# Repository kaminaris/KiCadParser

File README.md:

# kicad-io

TypeScript library for parsing, modifying, and serialising KiCad S-expression
files (`.kicad_sch`, `.kicad_pcb`, `.kicad_sym`).

The library is **source-only** — there is no root `package.json`. Consuming
projects reference it via TypeScript project references (`tsconfig.json`
`references` array).

---

## Overview

KiCad stores schematics, boards, and symbol libraries as S-expression (sexpr)
text files.  This library turns those files into a typed, navigable tree of
`KicadElement` objects, lets you inspect and modify the tree, and writes it
back to a valid KiCad file.

```
parse(text) → KicadElement tree → mutate → element.write() → text
```

---

## Structure

```
src/
  KicadParser.ts          # tokeniser + recursive-descent S-expr parser
  KicadElement.ts         # base class for every tree node
  KicadElement*.ts        # ~70 typed element subclasses
  Project/
    KicadSExprFile.ts     # abstract base: load → parse → write
    KicadSchematic.ts     # .kicad_sch loader, resolves hierarchical sheets
    KicadBoard.ts         # .kicad_pcb loader
    KicadProject.ts       # ties a schematic + board together
    SymbolBOMInterface.ts # BOM row shape + groupBOM() helper
    PathUtils.ts          # platform-agnostic path helpers
  Builder/
    PassiveSymbolBuilder.ts   # entry point – re-exports all builder APIs
    PassiveSymbolFromSpec.ts  # build a Device:* symbol from a spec object
    PassiveSymbolManualVariants.ts
    PassiveSymbolPrimitives.ts
    PassiveSymbolRegistry.ts
    PassiveSymbolTypes.ts
  Catalog/
    DeviceSymbolSpecs.ts      # geometry specs extracted from real KiCad files
    DevicePassiveSymbols.ts
    DeviceSymbolSpecTypes.ts
examples/                 # six runnable, heavily-commented example scripts
test/                     # vitest test suite
```

---

## Core API

### `KicadParser`

```ts
import { KicadParser } from './src/KicadParser';

const parser = new KicadParser();
const root = parser.parse(fileText);  // returns KicadElement
```

The parser recognises ~80 named element types via its `nodeMap` and
instantiates the appropriate subclass for each.  Unknown element names fall
back to the base `KicadElement`.

A `contextualNodeMap` handles the handful of element names whose meaning
depends on their parent (e.g. `unit` inside `units` vs. `unit` on a symbol
instance).

### `KicadElement`

The base class for every node in the tree.

| Method | Description |
|---|---|
| `findFirstChildByClass(Cls)` | First direct child that is an instance of `Cls` |
| `findChildrenByClass(Cls)` | All direct children that are instances of `Cls` |
| `findAllChildrenByClass(Cls)` | Deep search for all descendants of type `Cls` |
| `findOrCreateChildByClass(Cls)` | Find or lazily create a child of type `Cls` |
| `findFirstChildByName(name)` | First direct child with the given element name |
| `findAllChildrenByName(name)` | Deep search by element name |
| `setSimpleChild(name, value, format)` | Set/create a single-attribute leaf child |
| `getSimpleChildValue(name)` | Read the first attribute of a named child |
| `addChild(node)` | Append a child (sets `parent` + `rootLevel`) |
| `write()` | Serialise this node and all descendants back to KiCad text |

### Loading a file (`KicadSExprFile`)

The loader is I/O-agnostic — you supply a `loadFile` callback so the same code
works in Node.js, a browser, or any other runtime.

```ts
import { KicadSchematic } from './src/Project/KicadSchematic';

const sch = new KicadSchematic();
sch.loadFile = (path) => fs.promises.readFile(path, 'utf8');
sch.pathUtils = { dirname: (p) => path.dirname(p), join: (...parts) => path.join(...parts) };
await sch.loadFromPath('/path/to/my.kicad_sch');

const root = sch.rootElement!;
// navigate / modify ...
const updated = root.write();
await fs.promises.writeFile('/path/to/my.kicad_sch', updated, 'utf8');
```

### Loading a hierarchical project (`KicadProject`)

```ts
import { KicadProject } from './src/Project/KicadProject';

const project = new KicadProject();
await project.loadFromPath(loadFile, pathUtils, 'root.kicad_sch', 'board.kicad_pcb');

const schematic = project.mainSchematic!;
const board     = project.mainBoard!;
```

`KicadSchematic` automatically follows `sheet` references and populates
`schematic.sheets` with the parsed child schematics.

### Programmatic symbol building (`Builder`)

```ts
import { buildDeviceSymbolFromSpec } from './src/Builder/PassiveSymbolBuilder';

const symbol = buildDeviceSymbolFromSpec('R', '100k', '0402');
libSymbols.addChild(symbol);
```

See `examples/06-add-footprint-with-3d-model.ts` for a full walkthrough.

---

## Examples

Self-contained, runnable scripts in `examples/`:

```sh
cd examples
yarn install
yarn 01   # parse a schematic, list placed symbols
yarn 02   # parse a board, list layers + footprints
yarn 03   # load, modify a symbol's Value, write back out
yarn 04   # build a board layer stackup from scratch
yarn 05   # load a hierarchical multi-sheet project, print a BOM
yarn 06   # add a footprint with a 3D model reference from scratch
```

---

## Tests

```sh
cd test
yarn install
yarn test          # run once
yarn test:watch    # watch mode
```

The test suite uses [Vitest](https://vitest.dev/) and covers the tokeniser,
parser round-trips, element builders, and real-world KiCad 10 fixture files.

---

## License

MIT — see [LICENSE](LICENSE).

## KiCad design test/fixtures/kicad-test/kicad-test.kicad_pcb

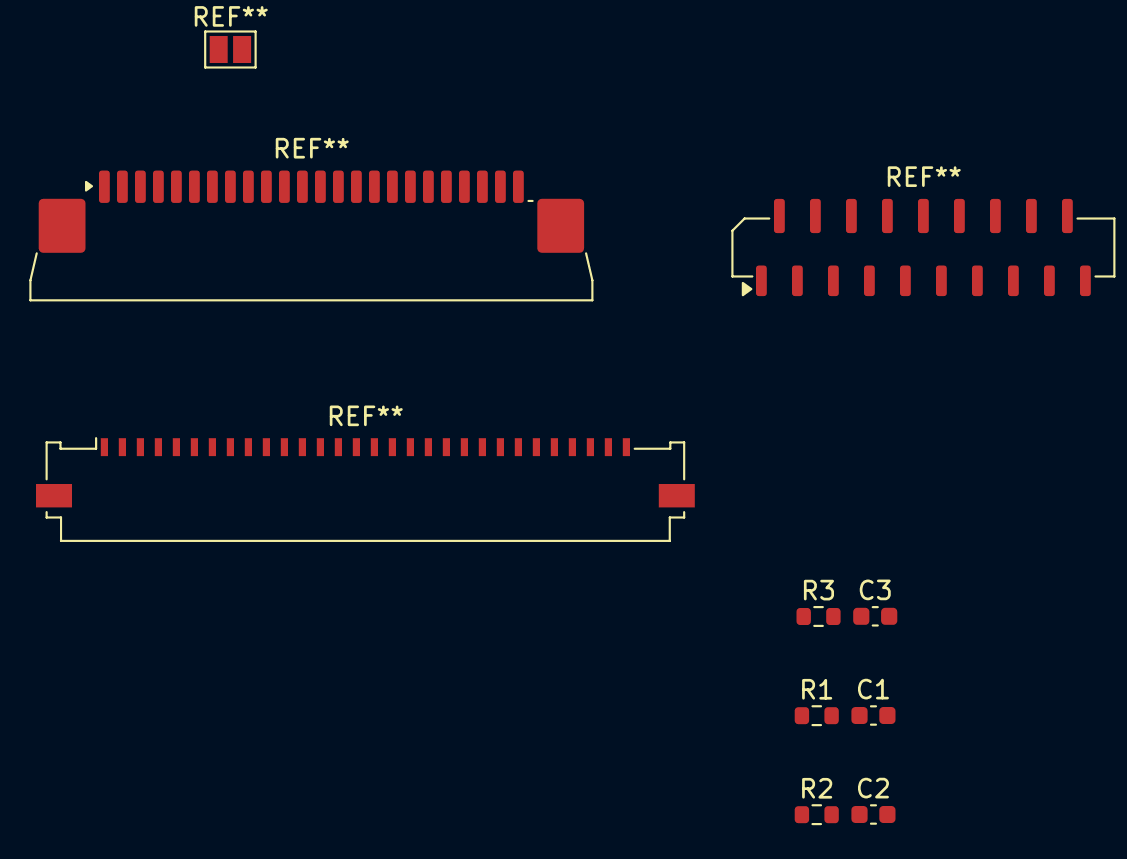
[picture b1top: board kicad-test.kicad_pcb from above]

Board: 2 copper layers, 6 parts (0 on the bottom side), 5 nets, no tracks yet.

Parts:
C1, C2, C3: C; C_0603_1608Metric
R1, R2, R3: R; R_0603_1608Metric

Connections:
+3.3V: R1.1, R2.1, R3.1
/TestSheet1/hiera: C1.1, R1.2
/TestSheet2/hiera: C2.1, R2.2
/TestSheet3/hiera: C3.1, R3.2
GND: C1.2, C2.2, C3.2

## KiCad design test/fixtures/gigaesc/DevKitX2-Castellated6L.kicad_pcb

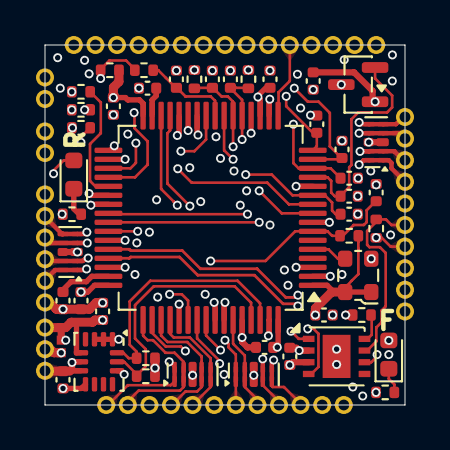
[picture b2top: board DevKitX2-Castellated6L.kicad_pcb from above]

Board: 6 copper layers, 20.0 x 20.0 mm, 47 parts (0 on the bottom side), 65 nets.

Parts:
C1, C2, C3, C25, C26, C27, C28, C47, C48, C49: 100n; C_0402_1005Metric
C5, C6, C15, C16, C17, C18, C19, C20: 1u; C_0402_1005Metric
C29, C30: 1n; C_0402_1005Metric
D1: L RUN; LED_0603_1608Metric
D2: L FAULT; LED_0603_1608Metric
J4: X3.0CH-Master
JP3: VSel; SolderJumper-3-0.5-Small
R1, R2: 3.3k; R_0402_1005Metric
R3, R10, R11, R12, R13, R14: 10k; R_0402_1005Metric
R4: 120; R_0402_1005Metric
R8, R9: 100k; R_0402_1005Metric
R15, R16, R17: 1k; R_0402_1005Metric
U1: LSM6DS3TR-C; LGA-14_3x2.5mm_P0.5mm
U2: SIT3051; DFN-8-1EP_3x3mm_P0.65mm_EP1.55x2.4mm
U3: REF3033AIDBZR; SOT-23
U4, U5, U7, U8: PESD4USB5U-TTSX; Diodes_UDFN-10_1x2.5mm_P0.5mm
U6: STM32F405RGT6; LQFP-64_10x10mm_P0.5mm
Y1: SX2M8.000M20F30TNN; Oscillator_SMD_ECS_2520MV-xxx-xx-4Pin_2.5x2.0mm

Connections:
+3.3REF: C6.1, U3.2 (Vout), U6.13 (VDDA)
+3.3V: C1.1, C2.1, C3.1, C17.1, C18.1, C19.1, C20.1, C47.1, J4.11 (3.3V), JP3.1 (A), R1.1, R2.1, R10.1, R13.2, U1.5 (VDDIO), U1.8 (VDD), U1.12 (CS), U2.3 (VDD), U6.1 (VBAT), U6.19 (VDD), U6.32 (VDD), U6.48 (VDD), U6.64 (VDD), Y1.1 (Tri-State), Y1.4 (VDD)
+5V: C5.1, J4.12 (5V), JP3.3 (B), U3.1 (Vin)
CAN RX: U2.4 (RXD), U6.57 (PB5)
CAN TX: U2.1 (TXD), U6.58 (PB6)
CURR1 FILTERED: J4.37 (CURRENT1), U6.8 (PC0)
CURR2 FILTERED: J4.42 (CURRENT2), U6.9 (PC1)
CURR3 FILTERED: J4.47 (CURRENT3), U6.10 (PC2)
ESP-RX: J4.18 (U1-RX), U6.52 (PC11), U7.5, U7.6
ESP-TX: J4.17 (U1-TX), U6.51 (PC10), U7.4, U7.7
GND: C1.2, C2.2, C3.2, C5.2, C6.2, C15.2, C16.2, C17.2, C18.2, C19.2, C20.2, C25.2, C29.2, C30.2, C47.2, C48.2, C49.2, J4.3 (GND), J4.10 (GND), J4.13 (GND), J4.16 (GND), J4.28 (GND), J4.31 (GND), R3.1, R8.1, R9.2, R11.2, R12.2, U1.1 (SDO/SA0), U1.2 (SDX), U1.3 (SCX), U1.6 (GND), U1.7 (GND), U2.2 (VSS), U2.9 (VSS), U3.3 (GND), U4.3 (VSS), U4.8 (VSS), U5.3 (VSS), U5.8 (VSS), U6.12 (VSSA), U6.18 (VSS), U6.28 (PB2), U6.60 (BOOT0), U6.63 (VSS), U7.3 (VSS), U7.8 (VSS), U8.3 (VSS), U8.8 (VSS), Y1.2 (GND)
H1: J4.39 (H1), U6.41 (PA8)
H2: J4.44 (H2), U6.42 (PA9)
H3: J4.49 (H3), U6.43 (PA10)
HALL1: R17.1, U6.37 (PC6)
HALL1 IN: J4.6 (HALL1), R17.2, U8.5, U8.6
HALL2: R16.1, U6.38 (PC7)
HALL2 IN: J4.7 (HALL2), R16.2, U8.4, U8.7
HALL3: R15.1, U6.39 (PC8)
HALL3 IN: J4.8 (HALL3), R15.2, U8.2, U8.9
HALL-VOLTAGE: J4.5 (HALL-VCC), JP3.2 (C)
I2C2 SCL/USART3 TX: J4.23 (U3-TX), U5.5, U5.6, U6.29 (PB10)
I2C2 SDA/USART3 RX: J4.22 (U3-RX), U5.4, U5.7, U6.30 (PB11)
IMU SCL: R2.2, U1.13 (SCL), U6.61 (PB8)
IMU SDA: R1.2, U1.14 (SDA), U6.62 (PB9)
IN V: C30.1, J4.4 (IN-V), U6.11 (PC3)
IN-CANH: J4.30 (CANH), R4.2, U2.7 (CANH)
IN-CANL: J4.29 (CANL), R4.1, U2.6 (CANL)
L1: J4.38 (L1), U6.34 (PB13)
L2: J4.43 (L2), U6.35 (PB14)
L3: J4.48 (L3), U6.36 (PB15)
LED FAULT: D2.2 (A), U6.53 (PC12)
LED RUN: D1.2 (A), U6.54 (PD2)
MOSTEMP1: J4.40 (TEMP1), U6.17 (PA3)
MOSTEMP2: J4.45 (TEMP2), U6.26 (PB0)
MOSTEMP3: J4.50 (TEMP3), U6.27 (PB1)
NRST: C25.1, J4.20 (NRST), R10.2, U5.1, U5.10, U6.7 (NRST)
unnamed: D1.1 (K), R11.1
unnamed: D2.1 (K), R12.1
unnamed: R3.2, U2.8 (S)
unnamed: U6.5 (PH0), Y1.3 (OUT)
unnamed: C15.1, U6.31 (VCAP_1)
unnamed: C16.1, U6.47 (VCAP_2)
PHASE FILTER ENABLE1: C26.2, U6.40 (PC9)
PHASE FILTER ENABLE2: C27.2, U6.2 (PC13)
PHASE FILTER ENABLE3: C28.2, U6.3 (PC14)
POWER STAGE DISABLE: J4.1 (POWER_STAGE_DISABLE), U6.25 (PC5)
POWER STAGE LOCKOUT: J4.2 (POWER_STAGE_LOCKOUT), U6.33 (PB12)
RESERVED1: J4.19 (RESERVED1), U6.50 (PA15)
RESERVED2: J4.24 (RESERVED2), U6.55 (PB3)
RESERVED3: J4.25 (RESERVED3), U6.56 (PB4)
SERVO: J4.21 (SERVO), U5.2, U5.9, U6.59 (PB7)
SPI1-MISO-ADC2: C48.1, J4.33 (MISO/ADC2), R9.1, U4.2, U4.9, U6.22 (PA6)
SPI1-MOSI: J4.32 (MOSI), U4.1, U4.10, U6.23 (PA7)
SPI1-NSS: J4.35 (NSS), U4.5, U4.6, U6.20 (PA4)
SPI1-SCK-ADC: C49.1, J4.34 (SCK/ADC), R8.2, U4.4, U4.7, U6.21 (PA5)
SWCLK: J4.15 (CLK), U6.49 (PA14), U7.2, U7.9
SWDIO: J4.14 (DIO), U6.46 (PA13), U7.1, U7.10
TEMPMOTOR: C29.1, R14.2, U6.24 (PC4)
TEMPMOTOR IN: J4.9 (TEMP-MOTOR), R13.1, R14.1, U8.1, U8.10
USBD+: J4.26 (USBD+), U6.45 (PA12)
USBD-: J4.27 (USBD-), U6.44 (PA11)
VSENSE1: C26.1, J4.36 (VSENSE1), U6.14 (PA0)
VSENSE2: C27.1, J4.41 (VSENSE2), U6.15 (PA1)
VSENSE3: C28.1, J4.46 (VSENSE3), U6.16 (PA2)

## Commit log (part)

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2025-09-29 initial
2025-09-29 Add MIT License to the project
2025-09-29 kicad lib fixes
2025-10-07 kicad lib up
2025-10-07 import fixes
2025-10-08 condensed classes
2025-10-08 arc testing
2025-10-08 arc and bezier
2025-10-08 symbol units
2025-10-10 Mixin pattern
2025-10-11 board elements
2025-10-19 project upgrade
2025-10-19 board and schematic
2025-10-20 nested sheet fix
